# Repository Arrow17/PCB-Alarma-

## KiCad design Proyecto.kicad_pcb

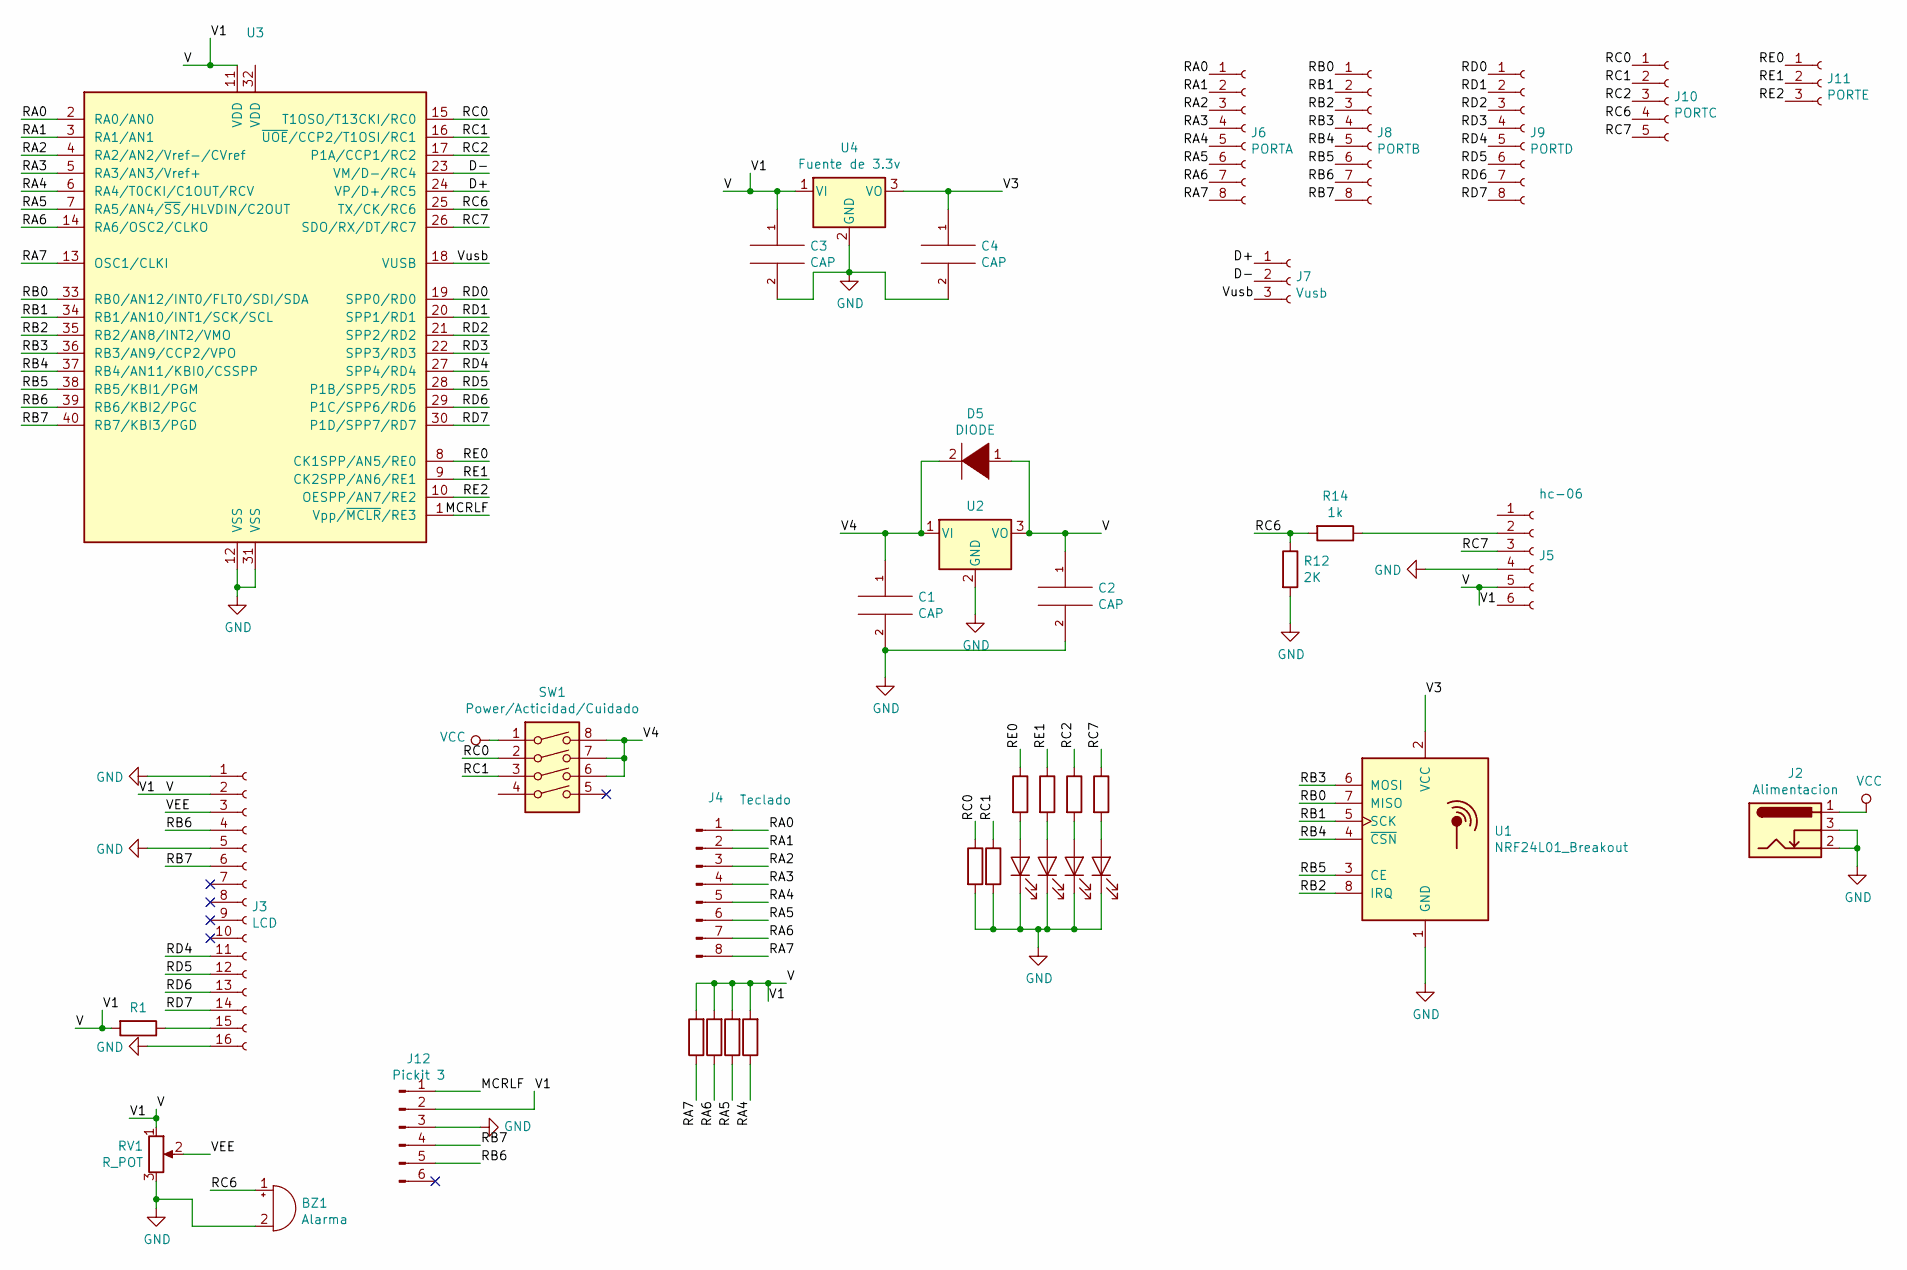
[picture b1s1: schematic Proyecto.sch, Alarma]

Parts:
BZ1: Alarma; Buzzer_12x9.5RM7.6
C1, C2: CAP; C_Disc_D5.0mm_W2.5mm_P5.00mm
C3, C4: CAP; CP_Radial_D5.0mm_P2.00mm
D1, D2, D3, D4: LED; LED_D3.0mm_FlatTop
D5: DIODE; R_Axial_DIN0204_L3.6mm_D1.6mm_P7.62mm_Horizontal
J2: Alimentacion; BarrelJack_Wuerth_6941xx301002
J3: LCD; PinSocket_1x16_P2.54mm_Vertical
J4: Teclado; PinHeader_1x08_P2.54mm_Vertical
J5: hc-06; PinSocket_1x06_P2.54mm_Vertical
J6: PORTA; PinSocket_1x08_P2.54mm_Vertical
J7: Vusb; PinSocket_1x03_P2.54mm_Vertical
J8: PORTB; PinSocket_1x08_P2.54mm_Vertical
J9: PORTD; PinSocket_1x08_P2.54mm_Vertical
J10: PORTC; PinSocket_1x05_P2.54mm_Vertical
J11: PORTE; PinSocket_1x03_P2.54mm_Vertical
J12: Pickit 3; PinHeader_1x06_P2.54mm_Vertical
R1, R2, R3, R6, R7, R8, R9, R10, R11: R; R_Axial_DIN0207_L6.3mm_D2.5mm_P7.62mm_Horizontal
R4, R5: 10K; R_Axial_DIN0207_L6.3mm_D2.5mm_P7.62mm_Horizontal
R12: 2K; R_Axial_DIN0207_L6.3mm_D2.5mm_P7.62mm_Horizontal
R14: 1k; R_Axial_DIN0207_L6.3mm_D2.5mm_P7.62mm_Horizontal
RV1: R_POT; Potentiometer_Vishay_148-149_Single_Horizontal
SW1: Power/Acticidad/Cuidado; SW_DIP_SPSTx04_Piano_10.8x11.72mm_W7.62mm_P2.54mm
U1: NRF24L01_Breakout; nRF24L01_Breakout
U2: Fuente de 9-5v; TO-220-3_Vertical
U3: PIC18F4550-IP; DIP-40_W15.24mm
U4: Fuente de 3.3v; TO-220-3_Vertical

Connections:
/D+: J7.1, U3.24 (VP/D+/RC5)
/D-: J7.2, U3.23 (VM/D-/RC4)
/MCRLF: J12.1, U3.1 (Vpp/~MCLR~/RE3)
/RA0: J4.1, J6.1, U3.2 (RA0/AN0)
/RA1: J4.2, J6.2, U3.3 (RA1/AN1)
/RA2: J4.3, J6.3, U3.4 (RA2/AN2/Vref-/CVref)
/RA3: J4.4, J6.4, U3.5 (RA3/AN3/Vref+)
/RA4: J4.5, J6.5, R5.1, U3.6 (RA4/T0CKI/C1OUT/RCV)
/RA5: J4.6, J6.6, R4.1, U3.7 (RA5/AN4/~SS~/HLVDIN/C2OUT)
/RA6: J4.7, J6.7, R3.1, U3.14 (RA6/OSC2/CLKO)
/RA7: J4.8, J6.8, R2.1, U3.13 (OSC1/CLKI)
/RB0: J8.1, U1.7 (MISO), U3.33 (RB0/AN12/INT0/FLT0/SDI/SDA)
/RB1: J8.2, U1.5 (SCK), U3.34 (RB1/AN10/INT1/SCK/SCL)
/RB2: J8.3, U1.8 (IRQ), U3.35 (RB2/AN8/INT2/VMO)
/RB3: J8.4, U1.6 (MOSI), U3.36 (RB3/AN9/CCP2/VPO)
/RB4: J8.5, U1.4 (~CSN), U3.37 (RB4/AN11/KBI0/CSSPP)
/RB5: J8.6, U1.3 (CE), U3.38 (RB5/KBI1/PGM)
/RB6: J3.4, J8.7, J12.5, U3.39 (RB6/KBI2/PGC)
/RB7: J3.6, J8.8, J12.4, U3.40 (RB7/KBI3/PGD)
/RC0: J10.1, R6.1, SW1.2, U3.15 (T1OSO/T13CKI/RC0)
/RC1: J10.2, R7.1, SW1.3, U3.16 (~UOE~/CCP2/T1OSI/RC1)
/RC2: J10.3, R10.1, U3.17 (P1A/CCP1/RC2)
/RC6: BZ1.1 (-), J10.4, R12.1, R14.2, U3.25 (TX/CK/RC6)
/RC7: J5.3, J10.5, R11.1, U3.26 (SDO/RX/DT/RC7)
/RD0: J9.1, U3.19 (SPP0/RD0)
/RD1: J9.2, U3.20 (SPP1/RD1)
/RD2: J9.3, U3.21 (SPP2/RD2)
/RD3: J9.4, U3.22 (SPP3/RD3)
/RD4: J3.11, J9.5, U3.27 (SPP4/RD4)
/RD5: J3.12, J9.6, U3.28 (P1B/SPP5/RD5)
/RD6: J3.13, J9.7, U3.29 (P1C/SPP6/RD6)
/RD7: J3.14, J9.8, U3.30 (P1D/SPP7/RD7)
/RE0: J11.1, R8.1, U3.8 (CK1SPP/AN5/RE0)
/RE1: J11.2, R9.1, U3.9 (CK2SPP/AN6/RE1)
/RE2: J11.3, U3.10 (OESPP/AN7/RE2)
/V: C2.1, C3.1, D5.1 (K), J3.2, J5.5, J12.2, R1.2, R2.2, R3.2, R4.2, R5.2, RV1.1, U2.3 (VO), U3.11 (VDD), U4.1 (VI)
/V3: C4.1, U1.2 (VCC), U4.3 (VO)
/V4: C1.1, D5.2 (A), SW1.6, SW1.7, SW1.8, U2.1 (VI)
/VEE: J3.3, RV1.2
/Vusb: J7.3, U3.18 (VUSB)
GND: BZ1.2 (+), C1.2, C2.2, C3.2, C4.2, D1.1 (K), D2.1 (K), D3.1 (K), D4.1 (K), J2.2, J2.3, J3.1, J3.5, J3.16, J5.4, J12.3, R6.2, R7.2, R12.2, RV1.3, U1.1 (GND), U2.2 (GND), U3.12 (VSS), U3.31 (VSS), U4.2 (GND)
unnamed: D1.2 (A), R8.2
unnamed: D2.2 (A), R9.2
unnamed: D3.2 (A), R10.2
unnamed: D4.2 (A), R11.2
unnamed: J3.15, R1.1
unnamed: J5.2, R14.1
VCC: J2.1, SW1.1

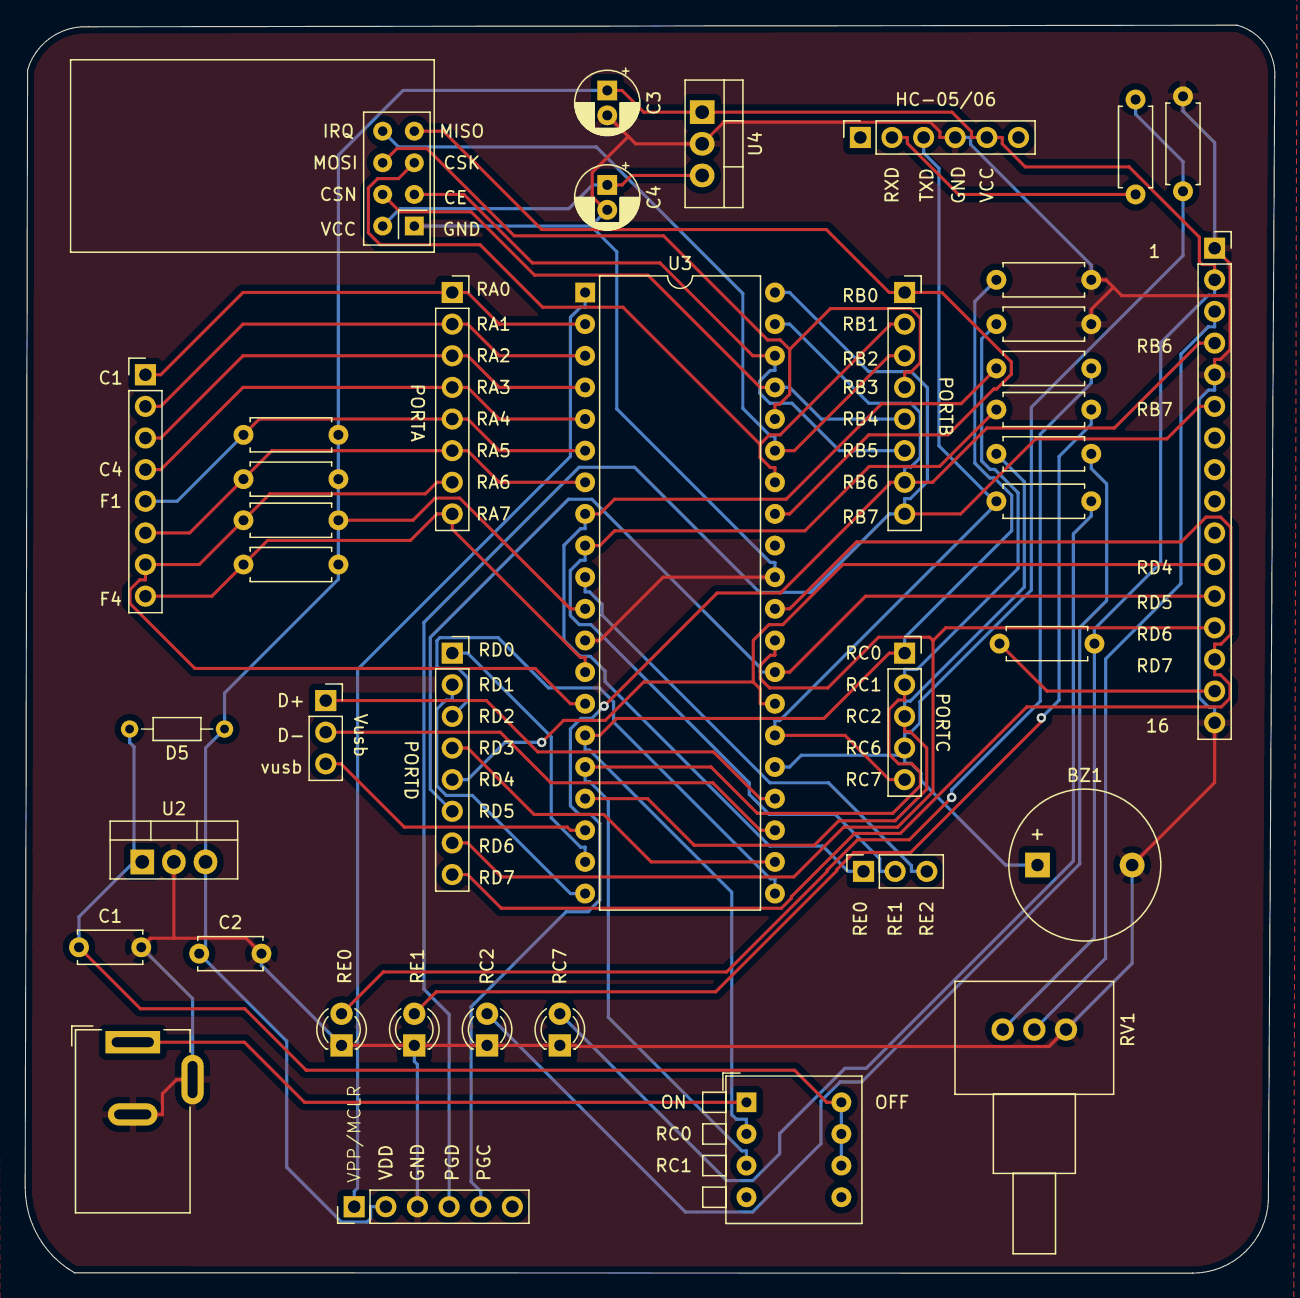
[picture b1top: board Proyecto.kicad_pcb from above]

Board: 2 copper layers, 100.3 x 100.2 mm, 40 parts (0 on the bottom side), 48 nets.

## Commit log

2019-04-29 Version 1.0
2019-04-29 version 1.5
2019-04-30 Correccion 1.0
